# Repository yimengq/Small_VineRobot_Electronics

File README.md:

# Board Design for Vine Robot:

## Overview:
### Gen 1 Board:
- Initially split into 4 total boards, 2 on outside for Sensing board + Power Module, and 2 on inside for POE communication board
- The external tip sensing board is designed based on ESP32 XIAO

### Gen 2 Board:

### Instructions  
To view video stream from ESP32-S3. 
- Follow instructions in ```Software/SoftwareSetup.txt``` to set up the ESP32-S3 and ESP32-EVB as a Wifi access point (Eth2Ap). 
- Upload ```Software/Arduino/CameraWebServer/CameraWebServer.ino``` onto ESP32-S3. 
- Run ```Software/videostream.py``` to view live video. 

### To Do (in progress)
- Achieve 1080p @ 30fps 
- Telemetry for IMU data 
- Two way http (send commands to ESP32-S3)

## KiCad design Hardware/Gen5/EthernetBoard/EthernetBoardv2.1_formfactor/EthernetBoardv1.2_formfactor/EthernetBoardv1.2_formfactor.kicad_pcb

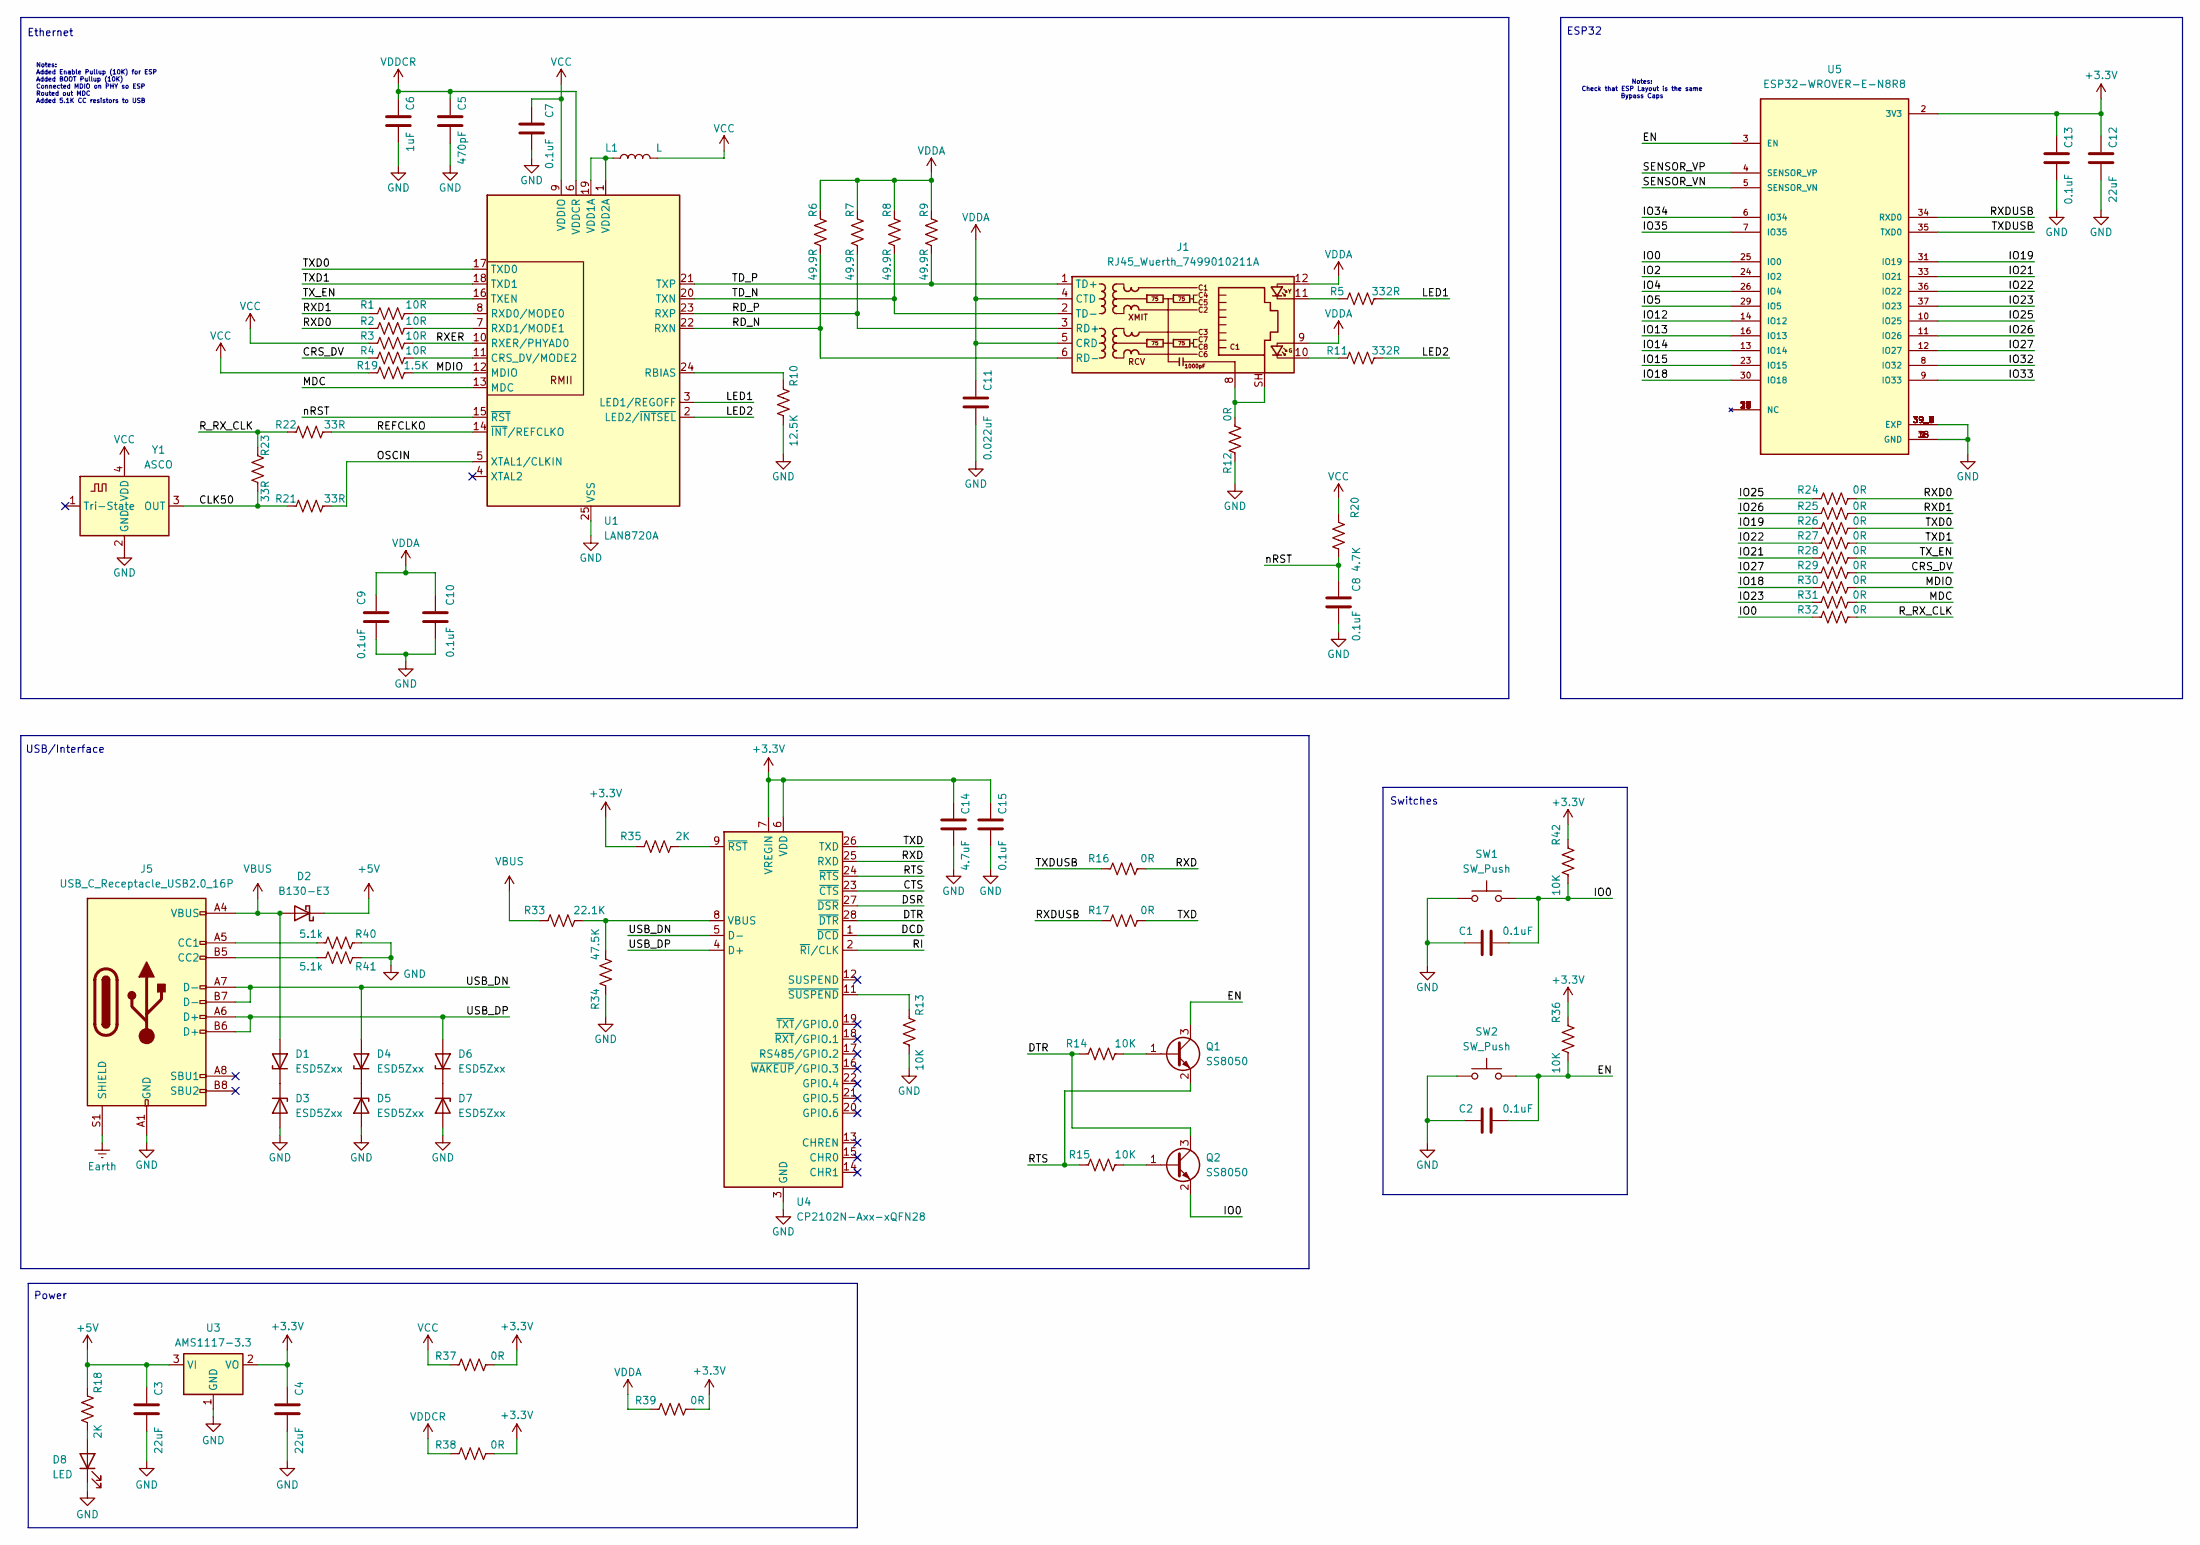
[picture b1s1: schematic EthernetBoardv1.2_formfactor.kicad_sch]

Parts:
C1, C2, C8, C9, C10, C13, C15: 0.1uF; C_0603_1608Metric
C3, C4, C12: 22uF; C_0603_1608Metric
C5: 470pF; C_0603_1608Metric
C6: 1uF; C_0402_1005Metric
C7: 0.1uF; C_0402_1005Metric
C11: 0.022uF; C_0805_2012Metric
C14: 4.7uF; R_0201_0603Metric
D1, D3, D4, D5, D6, D7: ESD5Zxx; D_SOD-523
D2: B130-E3; D_SMA
D8: LED; LED_0603_1608Metric
J1: RJ45_Wuerth_7499010211A; RJ45_Wuerth_7499010211A_Horizontal
J5: USB_C_Receptacle_USB2.0_16P; USB_C_Receptacle_GCT_USB4085
L1: L; L_0603_1608Metric
Q1, Q2: SS8050; SOT-23
R1, R2, R3, R4: 10R; R_0603_1608Metric
R5, R11: 332R; R_0603_1608Metric
R6, R7, R8, R9: 49.9R; R_0402_1005Metric
R10: 12.5K; R_0402_1005Metric
R12, R16, R17, R24, R25, R26, R27, R28, R29, R30, R31, R32, R37, R38, R39: 0R; R_0201_0603Metric
R13, R14, R15: 10K; R_0603_1608Metric
R18: 2K; R_0402_1005Metric
R19: 1.5K; R_0402_1005Metric
R20: 4.7K; R_0402_1005Metric
R21, R22, R23: 33R; R_0402_1005Metric
R33: 22.1K; R_0805_2012Metric
R34: 47.5K; R_0603_1608Metric
R35: 2K; R_0805_2012Metric
R36, R42: 10K; R_0402_1005Metric
R40, R41: 5.1k; R_0603_1608Metric
SW1, SW2: SW_Push; SW_SPST_PTS810
U1: LAN8720A; VQFN-24-1EP_4x4mm_P0.5mm_EP2.5x2.5mm_ThermalVias
U3: AMS1117-3.3; SOT-223-3_TabPin2
U4: CP2102N-Axx-xQFN28; QFN-28-1EP_5x5mm_P0.5mm_EP3.35x3.35mm
U5: ESP32-WROVER-E-N8R8; XCVR_ESP32-WROVER-E-N8R8; PARTREV 1.6
Y1: ASCO; Oscillator_SMD_Abracon_ASCO-4Pin_1.6x1.2mm

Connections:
+3.3V: C4.1, C12.1, C13.1, C14.1, C15.1, R35.1, R36.2, R37.2, R38.2, R39.2, R42.2, U3.2 (VO), U4.6 (VDD), U4.7 (VREGIN), U5.2 (3V3)
+5V: C3.1, D2.1 (K), R18.1, U3.3 (VI)
/CLK50: R21.2, R23.1, Y1.3 (OUT)
/CRS_DV: R4.2, R29.2
/CTS: U4.23 (~CTS)
/DCD: U4.1 (~DCD)
/DSR: U4.27 (~DSR)
/DTR: Q2.3 (C), R14.1, U4.28 (~DTR)
/EN: C2.2, Q1.3 (C), R36.1, SW2.2, U5.3 (EN)
/IO0: C1.2, Q2.2 (E), R32.1, R42.1, SW1.2, U5.25 (IO0)
/IO2: U5.24 (IO2)
/IO4: U5.26 (IO4)
/IO5: U5.29 (IO5)
/IO12: U5.14 (IO12)
/IO13: U5.16 (IO13)
/IO14: U5.13 (IO14)
/IO15: U5.23 (IO15)
/IO18: R30.1, U5.30 (IO18)
/IO19: R26.1, U5.31 (IO19)
/IO21: R28.1, U5.33 (IO21)
/IO22: R27.1, U5.36 (IO22)
/IO23: R31.1, U5.37 (IO23)
/IO25: R24.1, U5.10 (IO25)
/IO26: R25.1, U5.11 (IO26)
/IO27: R29.1, U5.12 (IO27)
/IO32: U5.8 (IO32)
/IO33: U5.9 (IO33)
/IO34: U5.6 (IO34)
/IO35: U5.7 (IO35)
/LED1: R5.1, U1.3 (LED1/REGOFF)
/LED2: R11.1, U1.2 (LED2/~INTSEL)
/MDC: R31.2, U1.13 (MDC)
/MDIO: R19.1, R30.2, U1.12 (MDIO)
/OSCIN: R21.1, U1.5 (XTAL1/CLKIN)
/RD_N: J1.6 (RD-), R6.2, U1.22 (RXN)
/RD_P: J1.3 (RD+), R7.2, U1.23 (RXP)
/REFCLKO: R22.1, U1.14 (~INT/REFCLKO)
/RI: U4.2 (~RI/CLK)
/RTS: Q1.2 (E), R15.1, U4.24 (~RTS)
/RXD: R16.2, U4.25 (RXD)
/RXD0: R2.2, R24.2
/RXD1: R1.1, R25.2
/RXDUSB: R17.1, U5.34 (RXD0)
/RXER: R3.1, U1.10 (RXER/PHYAD0)
/R_RX_CLK: R22.2, R23.2, R32.2
/SENSOR_VN: U5.5 (SENSOR_VN)
/SENSOR_VP: U5.4 (SENSOR_VP)
/TD_N: J1.2 (TD-), R8.2, U1.20 (TXN)
/TD_P: J1.1 (TD+), R9.2, U1.21 (TXP)
/TXD: R17.2, U4.26 (TXD)
/TXD0: R26.2, U1.17 (TXD0)
/TXD1: R27.2, U1.18 (TXD1)
/TXDUSB: R16.1, U5.35 (TXD0)
/TX_EN: R28.2, U1.16 (TXEN)
/USB_DN: D4.2 (A), J5.A7 (D-), J5.B7 (D-), U4.5 (D-)
/USB_DP: D6.2 (A), J5.A6 (D+), J5.B6 (D+), U4.4 (D+)
/nRST: C8.1, R20.1, U1.15 (~RST)
Earth: J5.S1 (SHIELD)
GND: C1.1, C2.1, C3.2, C4.2, C5.2, C6.2, C7.2, C8.2, C9.2, C10.2, C11.2, C12.2, C13.2, C14.2, C15.2, D3.2 (A), D5.2 (A), D7.2 (A), D8.1 (K), J5.A1 (GND), J5.A12 (GND), J5.B1 (GND), J5.B12 (GND), R10.2, R12.2, R13.2, R34.1, R40.1, R41.1, SW1.1, SW2.1, U1.25 (VSS), U3.1 (GND), U4.3 (GND), U4.29 (GND), U5.1 (GND), U5.15 (GND), U5.38 (GND), U5.39_1 (EXP), U5.39_2 (EXP), U5.39_3 (EXP), U5.39_4 (EXP), U5.39_5 (EXP), U5.39_6 (EXP), U5.39_7 (EXP), U5.39_8 (EXP), U5.39_9 (EXP), Y1.2 (GND)
unnamed: D1.1 (K), D3.1 (K)
unnamed: D4.1 (K), D5.1 (K)
unnamed: D6.1 (K), D7.1 (K)
unnamed: D8.2 (A), R18.2
unnamed: J1.8, J1.SH, R12.1
unnamed: J1.10, R11.2
unnamed: J1.11, R5.2
unnamed: J5.A5 (CC1), R40.2
unnamed: J5.B5 (CC2), R41.2
unnamed: Q1.1 (B), R14.2
unnamed: Q2.1 (B), R15.2
unnamed: R4.1, U1.11 (CRS_DV/MODE2)
unnamed: R10.1, U1.24 (RBIAS)
unnamed: R1.2, U1.8 (RXD0/MODE0)
unnamed: R2.1, U1.7 (RXD1/MODE1)
unnamed: L1.1, U1.1 (VDD2A), U1.19 (VDD1A)
unnamed: R33.2, R34.2, U4.8 (VBUS)
unnamed: R35.2, U4.9 (~RST)
unnamed: R13.1, U4.11 (~SUSPEND)
VBUS: D1.2 (A), D2.2 (A), J5.A4 (VBUS), J5.A9 (VBUS), J5.B4 (VBUS), J5.B9 (VBUS), R33.1
VCC: C7.1, L1.2, R3.2, R19.2, R20.2, R37.1, U1.9 (VDDIO), Y1.4 (VDD)
VDDA: C9.1, C10.1, C11.1, J1.4 (CTD), J1.5 (CRD), J1.9, J1.12, R6.1, R7.1, R8.1, R9.1, R39.1
VDDCR: C5.1, C6.1, R38.1, U1.6 (VDDCR)

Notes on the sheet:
Notes: Added Enable Pullup (10K) for ESP Added BOOT Pullup (10K) Connected MDIO on PHY so ESP Routed out MDC Added 5.1K CC resistors to USB
ESP32
Ethernet
USB/Interface
Notes: Check that ESP Layout is the same Bypass Caps
Power
Switches

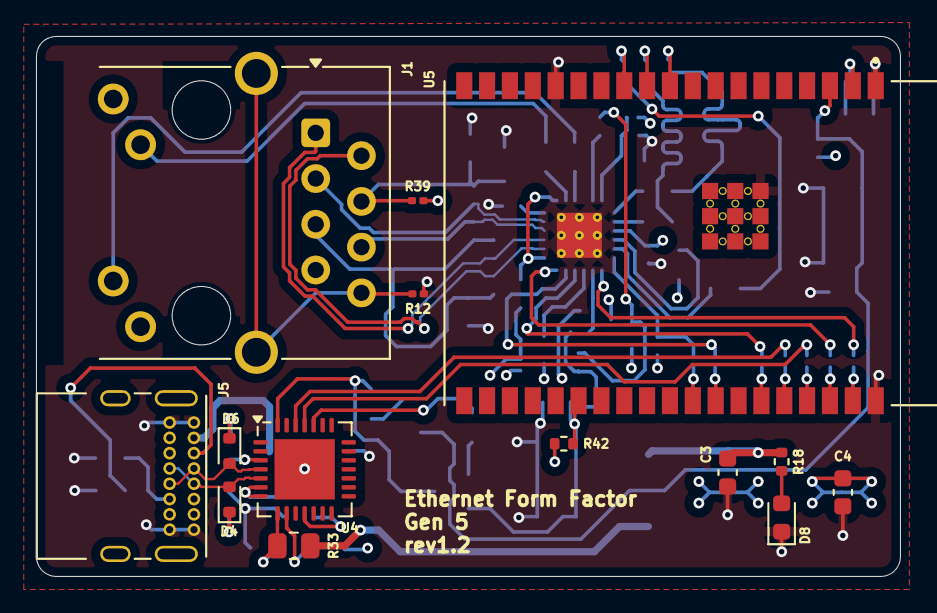
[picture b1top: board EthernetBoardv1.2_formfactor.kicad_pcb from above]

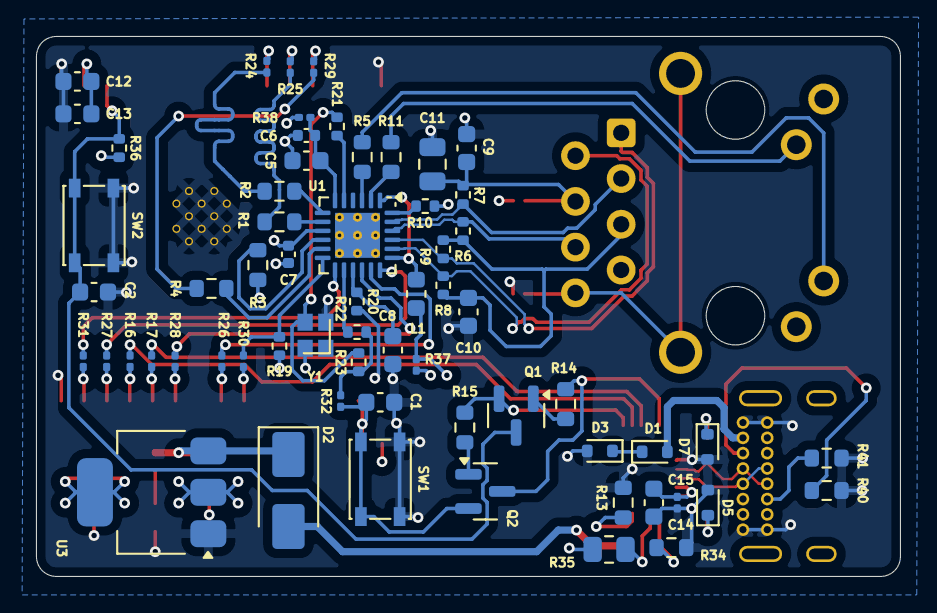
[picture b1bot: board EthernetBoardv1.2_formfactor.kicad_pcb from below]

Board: 4 copper layers, 48.0 x 30.0 mm, 77 parts (63 on the bottom side), 64 nets.

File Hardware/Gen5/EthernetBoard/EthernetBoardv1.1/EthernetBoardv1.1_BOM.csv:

"Id";"Designator";"Footprint";"Quantity";"Designation";"Supplier and ref";
1;"J1";"RJ45_Wuerth_7499010211A_Horizontal";1;"RJ45_Wuerth_7499010211A";;;
2;"C1,C2,C15,C13,C10,C9,C8,C7";"C_0603_1608Metric";8;"0.1uF";;;
3;"TP2,TP1";"TestPoint_Pad_2.0x2.0mm";2;"TestPoint";;;
4;"J6";"PinHeader_1x02_P2.54mm_Vertical";1;"Conn_01x02_Pin";;;
5;"J4";"PinHeader_2x07_P2.54mm_Vertical";1;"Conn_02x07_Odd_Even";;;
6;"R12,R17,R16,R27,R28,R25,R26,R30,R29,R31,R32,R24";"SolderJumper-2_P1.3mm_Bridged2Bar_RoundedPad1.0x1.5mm";12;"0R";;;
7;"R11,R5";"R_0603_1608Metric";2;"332R";;;
8;"R9,R8,R7,R6";"R_0402_1005Metric";4;"49.9R";;;
9;"C11";"C_0805_2012Metric";1;"0.022uF";;;
10;"R10";"R_0402_1005Metric";1;"12.5K";;;
11;"C5";"C_0603_1608Metric";1;"470pF";;;
12;"R20";"R_0402_1005Metric";1;"4.7K";;;
13;"R19";"R_0402_1005Metric";1;"1.5K";;;
14;"R23,R22,R21";"R_0402_1005Metric";3;"33R";;;
15;"SW2,SW1";"SW_SPST_PTS810";2;"SW_Push";;;
16;"J3,J2";"PinHeader_1x19_P2.54mm_Vertical";2;"Conn_01x19_Pin";;;
17;"R18";"R_0402_1005Metric";1;"2K";;;
18;"D8";"LED_0603_1608Metric";1;"LED";;;
19;"C12,C4,C3";"C_0603_1608Metric";3;"22uF";;;
20;"R13,R15,R14";"R_0603_1608Metric";3;"10K";;;
21;"C14";"R_0201_0603Metric";1;"4.7uF";;;
22;"R35";"R_0805_2012Metric";1;"2K";;;
23;"R34";"R_0603_1608Metric";1;"47.5K";;;
24;"R33";"R_0805_2012Metric";1;"22.1K";;;
25;"R4,R3,R2,R1";"R_0603_1608Metric";4;"10R";;;
26;"C6";"C_0402_1005Metric";1;"1uF";;;
27;"J5";"USB_C_Receptacle_GCT_USB4085";1;"USB_C_Receptacle_USB2.0_16P";;;
28;"D6,D3,D4,D1,D7,D5";"D_SOD-523";6;"ESD5Zxx";;;
29;"U5";"XCVR_ESP32-WROVER-E-N8R8";1;"ESP32-WROVER-E-N8R8";;;
30;"U3";"SOT-223-3_TabPin2";1;"AMS1117-3.3";;;
31;"D2";"D_SMA";1;"B130-E3";;;
32;"Q1,Q2";"SOT-23";2;"SS8050";;;
33;"U1";"VQFN-24-1EP_4x4mm_P0.5mm_EP2.5x2.5mm_ThermalVias";1;"LAN8720A";;;
34;"Y1";"Oscillator_SMD_Abracon_ASCO-4Pin_1.6x1.2mm";1;"ASCO";;;
35;"U4";"QFN-28-1EP_5x5mm_P0.5mm_EP3.35x3.35mm";1;"CP2102N-Axx-xQFN28";;;

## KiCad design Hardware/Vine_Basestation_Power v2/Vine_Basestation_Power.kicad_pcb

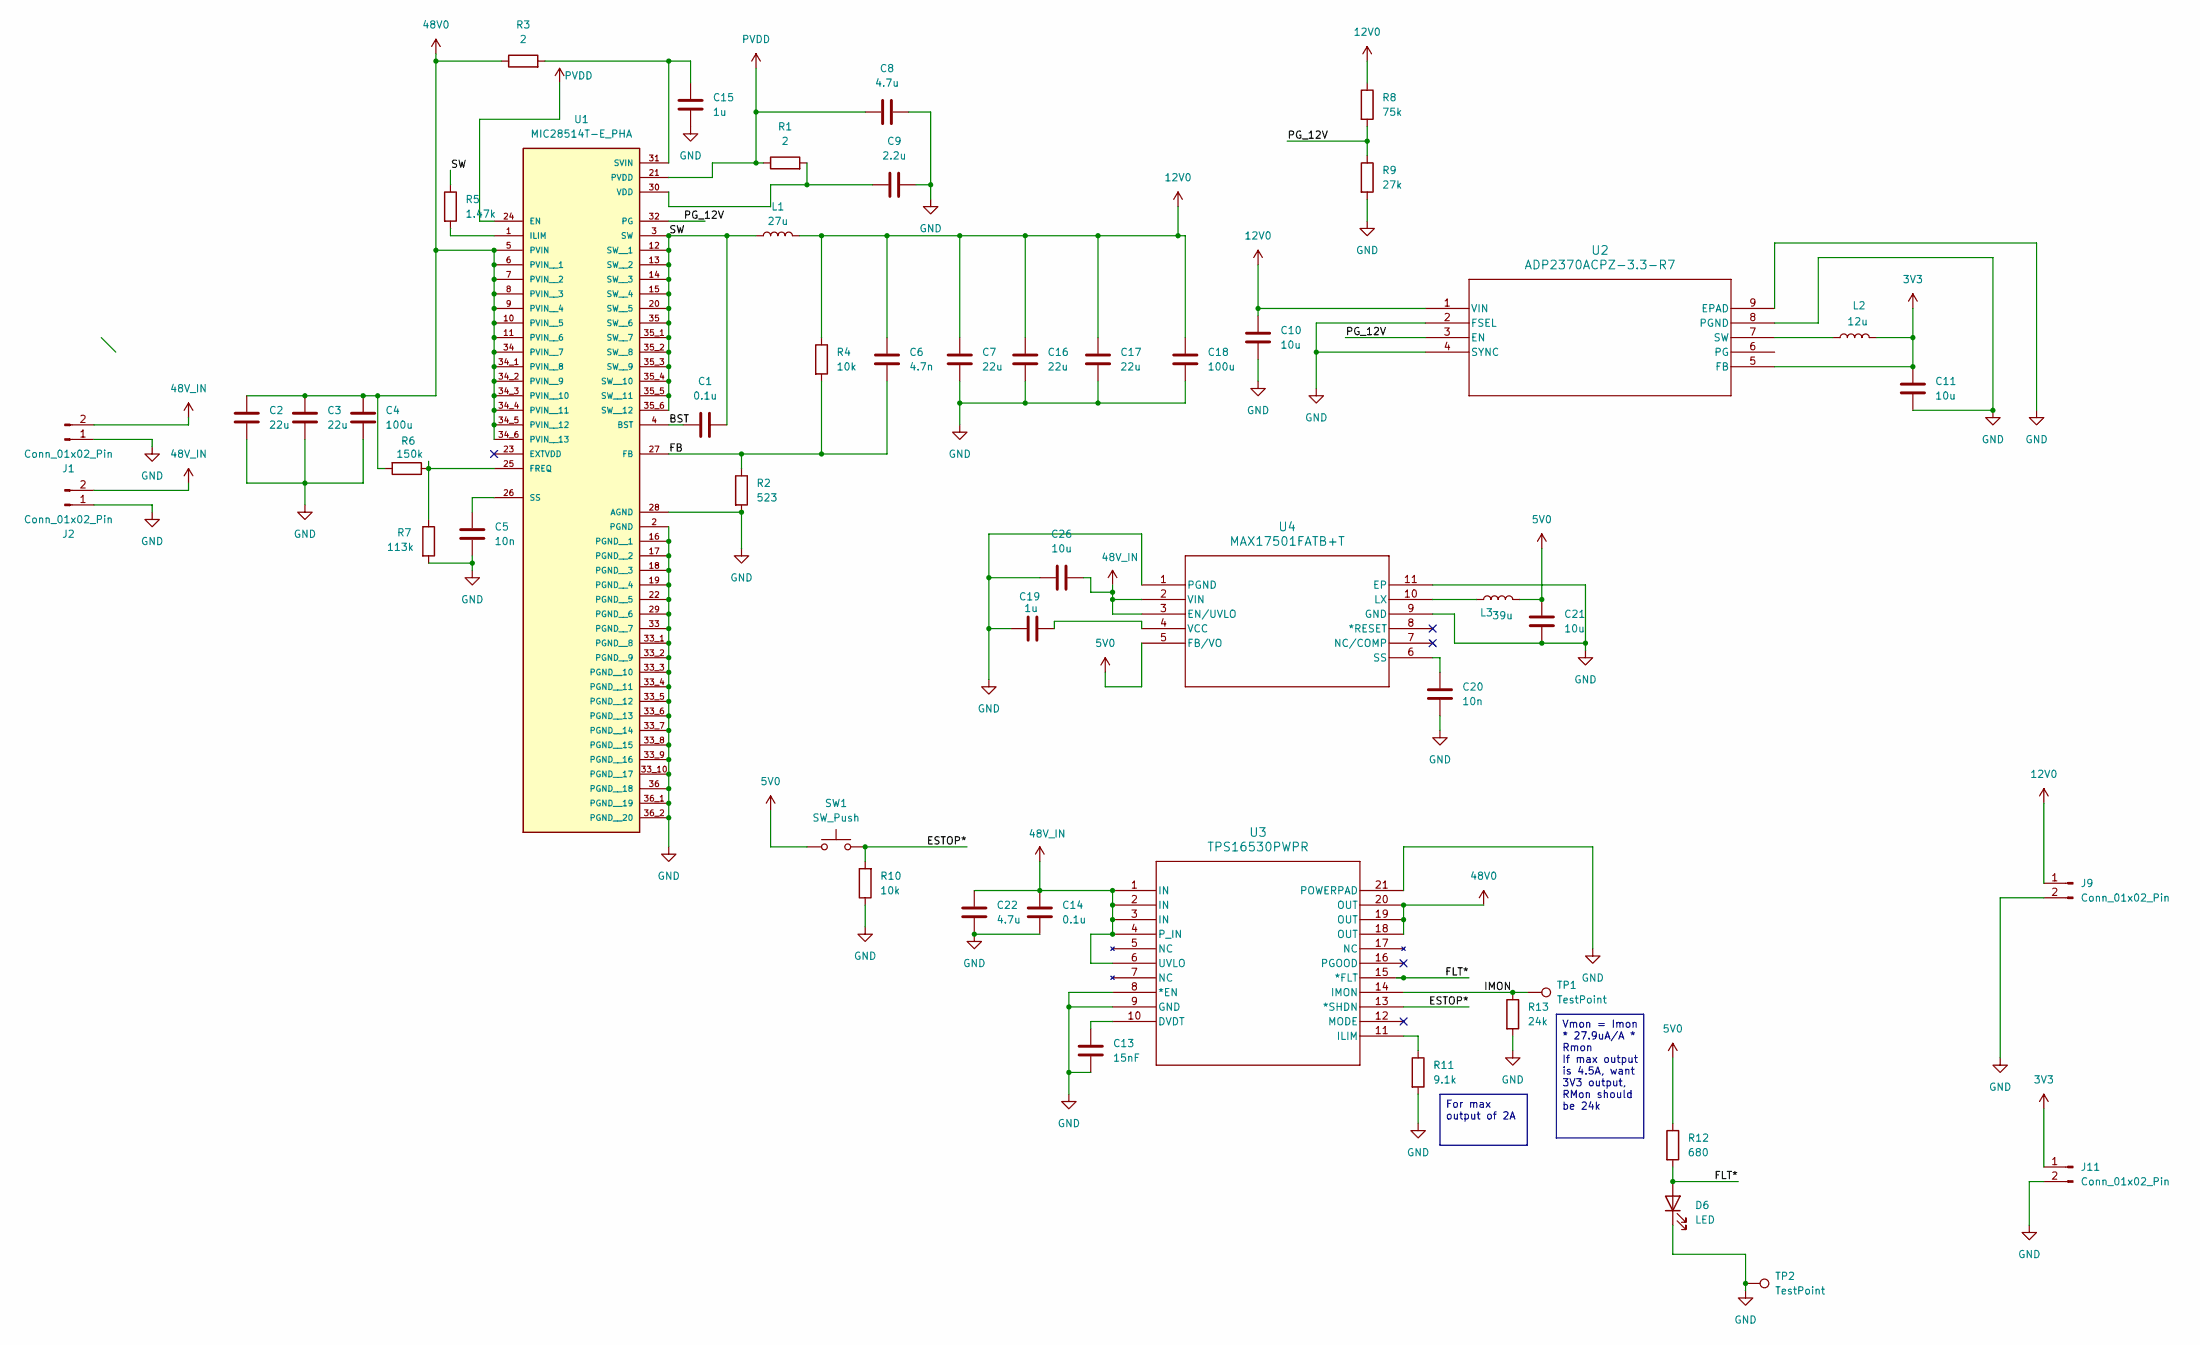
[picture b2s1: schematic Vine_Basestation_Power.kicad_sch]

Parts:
C1, C14: 0.1u; C_0402_1005Metric
C2, C3: 22u; CAP_EEETG2A220UP
C4: 100u; CAP_EEEFK1J101P
C5, C20: 10n; C_0402_1005Metric
C6: 4.7n; C_0402_1005Metric
C7, C16, C17: 22u; C_0805_2012Metric
C8: 4.7u; C_0402_1005Metric
C9: 2.2u; C_0402_1005Metric
C10, C11, C21, C26: 10u; C_0402_1005Metric
C13: 15nF; C_0402_1005Metric
C15, C19: 1u; C_0402_1005Metric
C18: 100u; CP_Radial_D5.0mm_P2.00mm
C22: 4.7u; C_0805_2012Metric
D6: LED; LED_0805_2012Metric
J1, J2: Conn_01x02_Pin; AMASS_XT30U-M_1x02_P5.0mm_Vertical
J9, J11: Conn_01x02_Pin; JST_PH_B2B-PH-SM4-TB_1x02-1MP_P2.00mm_Vertical
L1: 27u; INDM134126X600N
L2: 12u; IND_BOURNS_CC453232
L3: 39u; L_0805_2012Metric
R1, R3: 2; R_0402_1005Metric
R2: 523; R_0402_1005Metric
R4, R10: 10k; R_0402_1005Metric
R5: 1.47k; R_0402_1005Metric
R6: 150k; R_0402_1005Metric
R7: 113k; R_0402_1005Metric
R8: 75k; R_0402_1005Metric
R9: 27k; R_0402_1005Metric
R11: 9.1k; R_0402_1005Metric
R12: 680; R_0402_1005Metric
R13: 24k; R_0402_1005Metric
SW1: SW_Push; JST_PH_B2B-PH-SM4-TB_1x02-1MP_P2.00mm_Vertical
TP1, TP2: TestPoint; TestPoint_Loop_D1.80mm_Drill1.0mm_Beaded
U1: MIC28514T-E_PHA; CONV_MIC28514T-E_PHA; PARTREV E
U2: ADP2370ACPZ-3.3-R7; CP_8_5_ADI
U3: TPS16530PWPR; PWP0020T_TEX
U4: MAX17501FATB+T; 21-0429_T1032N&plus_1_MXM

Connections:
3V3: C11.1, J11.1, L2.2, U2.5 (FB)
5V0: C21.1, L3.2, R12.1, SW1.1, U4.5 (FB/VO)
12V0: C6.1, C7.1, C10.1, C16.1, C17.1, C18.1, J9.1, L1.2, R4.1, R8.1, U2.1 (VIN)
48V0: C2.1, C3.1, C4.1, R3.1, R6.2, U1.5 (PVIN), U1.6 (PVIN__1), U1.7 (PVIN__2), U1.8 (PVIN__3), U1.9 (PVIN__4), U1.10 (PVIN__5), U1.11 (PVIN__6), U1.34 (PVIN__7), U1.34_1 (PVIN__8), U1.34_2 (PVIN__9), U1.34_3 (PVIN__10), U1.34_4 (PVIN__11), U1.34_5 (PVIN__12), U1.34_6 (PVIN__13), U3.18 (OUT), U3.19 (OUT), U3.20 (OUT)
48V_IN: C14.1, C22.1, C26.1, J1.2, J2.2, U3.1 (IN), U3.2 (IN), U3.3 (IN), U3.4 (P_IN), U3.6 (UVLO), U4.2 (VIN), U4.3 (EN/UVLO)
/BST: C1.1, U1.4 (BST)
/ESTOP*: R10.2, SW1.2, U3.13 (*SHDN)
/FB: C6.2, R2.1, R4.2, U1.27 (FB)
/FLT*: D6.2 (A), R12.2, U3.15 (*FLT)
/IMON: R13.1, TP1.1, U3.14 (IMON)
/PG_12V: R8.2, R9.1, U1.32 (PG), U2.3 (EN)
/SW: C1.2, L1.1, R5.1, U1.3 (SW), U1.12 (SW__1), U1.13 (SW__2), U1.14 (SW__3), U1.15 (SW__4), U1.20 (SW__5), U1.35 (SW__6), U1.35_1 (SW__7), U1.35_2 (SW__8), U1.35_3 (SW__9), U1.35_4 (SW__10), U1.35_5 (SW__11), U1.35_6 (SW__12)
GND: C2.2, C3.2, C4.2, C5.2, C7.2, C8.2, C9.2, C10.2, C11.2, C13.2, C14.2, C15.2, C16.2, C17.2, C18.2, C19.1, C20.2, C21.2, C22.2, C26.2, D6.1 (K), J1.1, J2.1, J9.2, J11.2, R2.2, R7.2, R9.2, R10.1, R11.2, R13.2, TP2.1, U1.2 (PGND), U1.16 (PGND__1), U1.17 (PGND__2), U1.18 (PGND__3), U1.19 (PGND__4), U1.22 (PGND__5), U1.28 (AGND), U1.29 (PGND__6), U1.33 (PGND__7), U1.33_1 (PGND__8), U1.33_2 (PGND__9), U1.33_3 (PGND__10), U1.33_4 (PGND__11), U1.33_5 (PGND__12), U1.33_6 (PGND__13), U1.33_7 (PGND__14), U1.33_8 (PGND__15), U1.33_9 (PGND__16), U1.33_10 (PGND__17), U1.36 (PGND__18), U1.36_1 (PGND__19), U1.36_2 (PGND__20), U2.2 (FSEL), U2.4 (SYNC), U2.8 (PGND), U2.9 (EPAD), U3.8 (*EN), U3.9 (GND), U3.21 (POWERPAD), U4.1 (PGND), U4.9 (GND), U4.11 (EP)
unnamed: R6.1, R7.1, U1.25 (FREQ)
unnamed: R5.2, U1.1 (ILIM)
unnamed: C5.1, U1.26 (SS)
unnamed: C15.1, R3.2, U1.31 (SVIN)
unnamed: C9.1, R1.2, U1.30 (VDD)
unnamed: L2.1, U2.7 (SW)
unnamed: C13.1, U3.10 (DVDT)
unnamed: R11.1, U3.11 (ILIM)
unnamed: L3.1, U4.10 (LX)
unnamed: C20.1, U4.6 (SS)
unnamed: C19.2, U4.4 (VCC)
PVDD: C8.1, R1.1, U1.21 (PVDD), U1.24 (EN)

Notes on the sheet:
Vmon = Imon * 27.9uA/A * Rmon If max output is 4.5A, want 3V3 output, RMon should be 24k
For max output of 2A

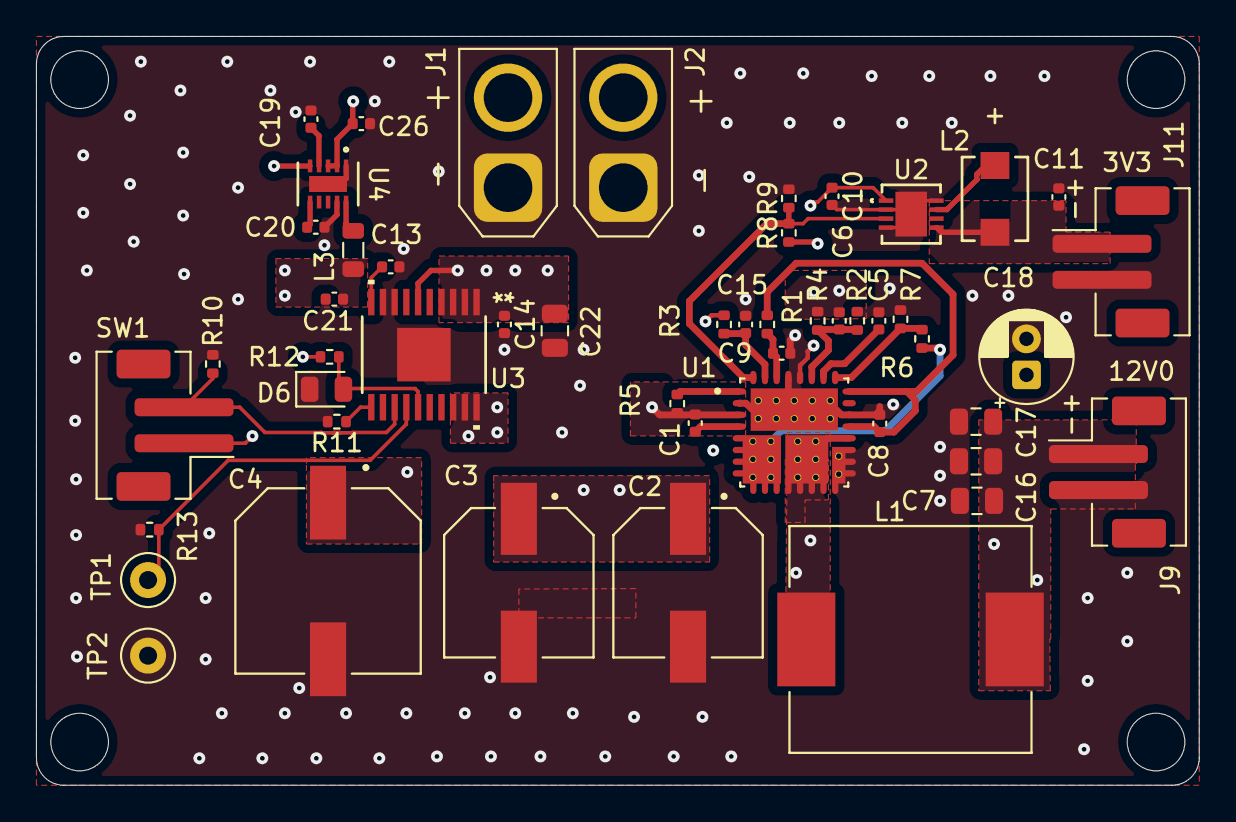
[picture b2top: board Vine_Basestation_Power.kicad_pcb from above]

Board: 4 copper layers, 64.6 x 41.6 mm, 50 parts (0 on the bottom side), 25 nets.

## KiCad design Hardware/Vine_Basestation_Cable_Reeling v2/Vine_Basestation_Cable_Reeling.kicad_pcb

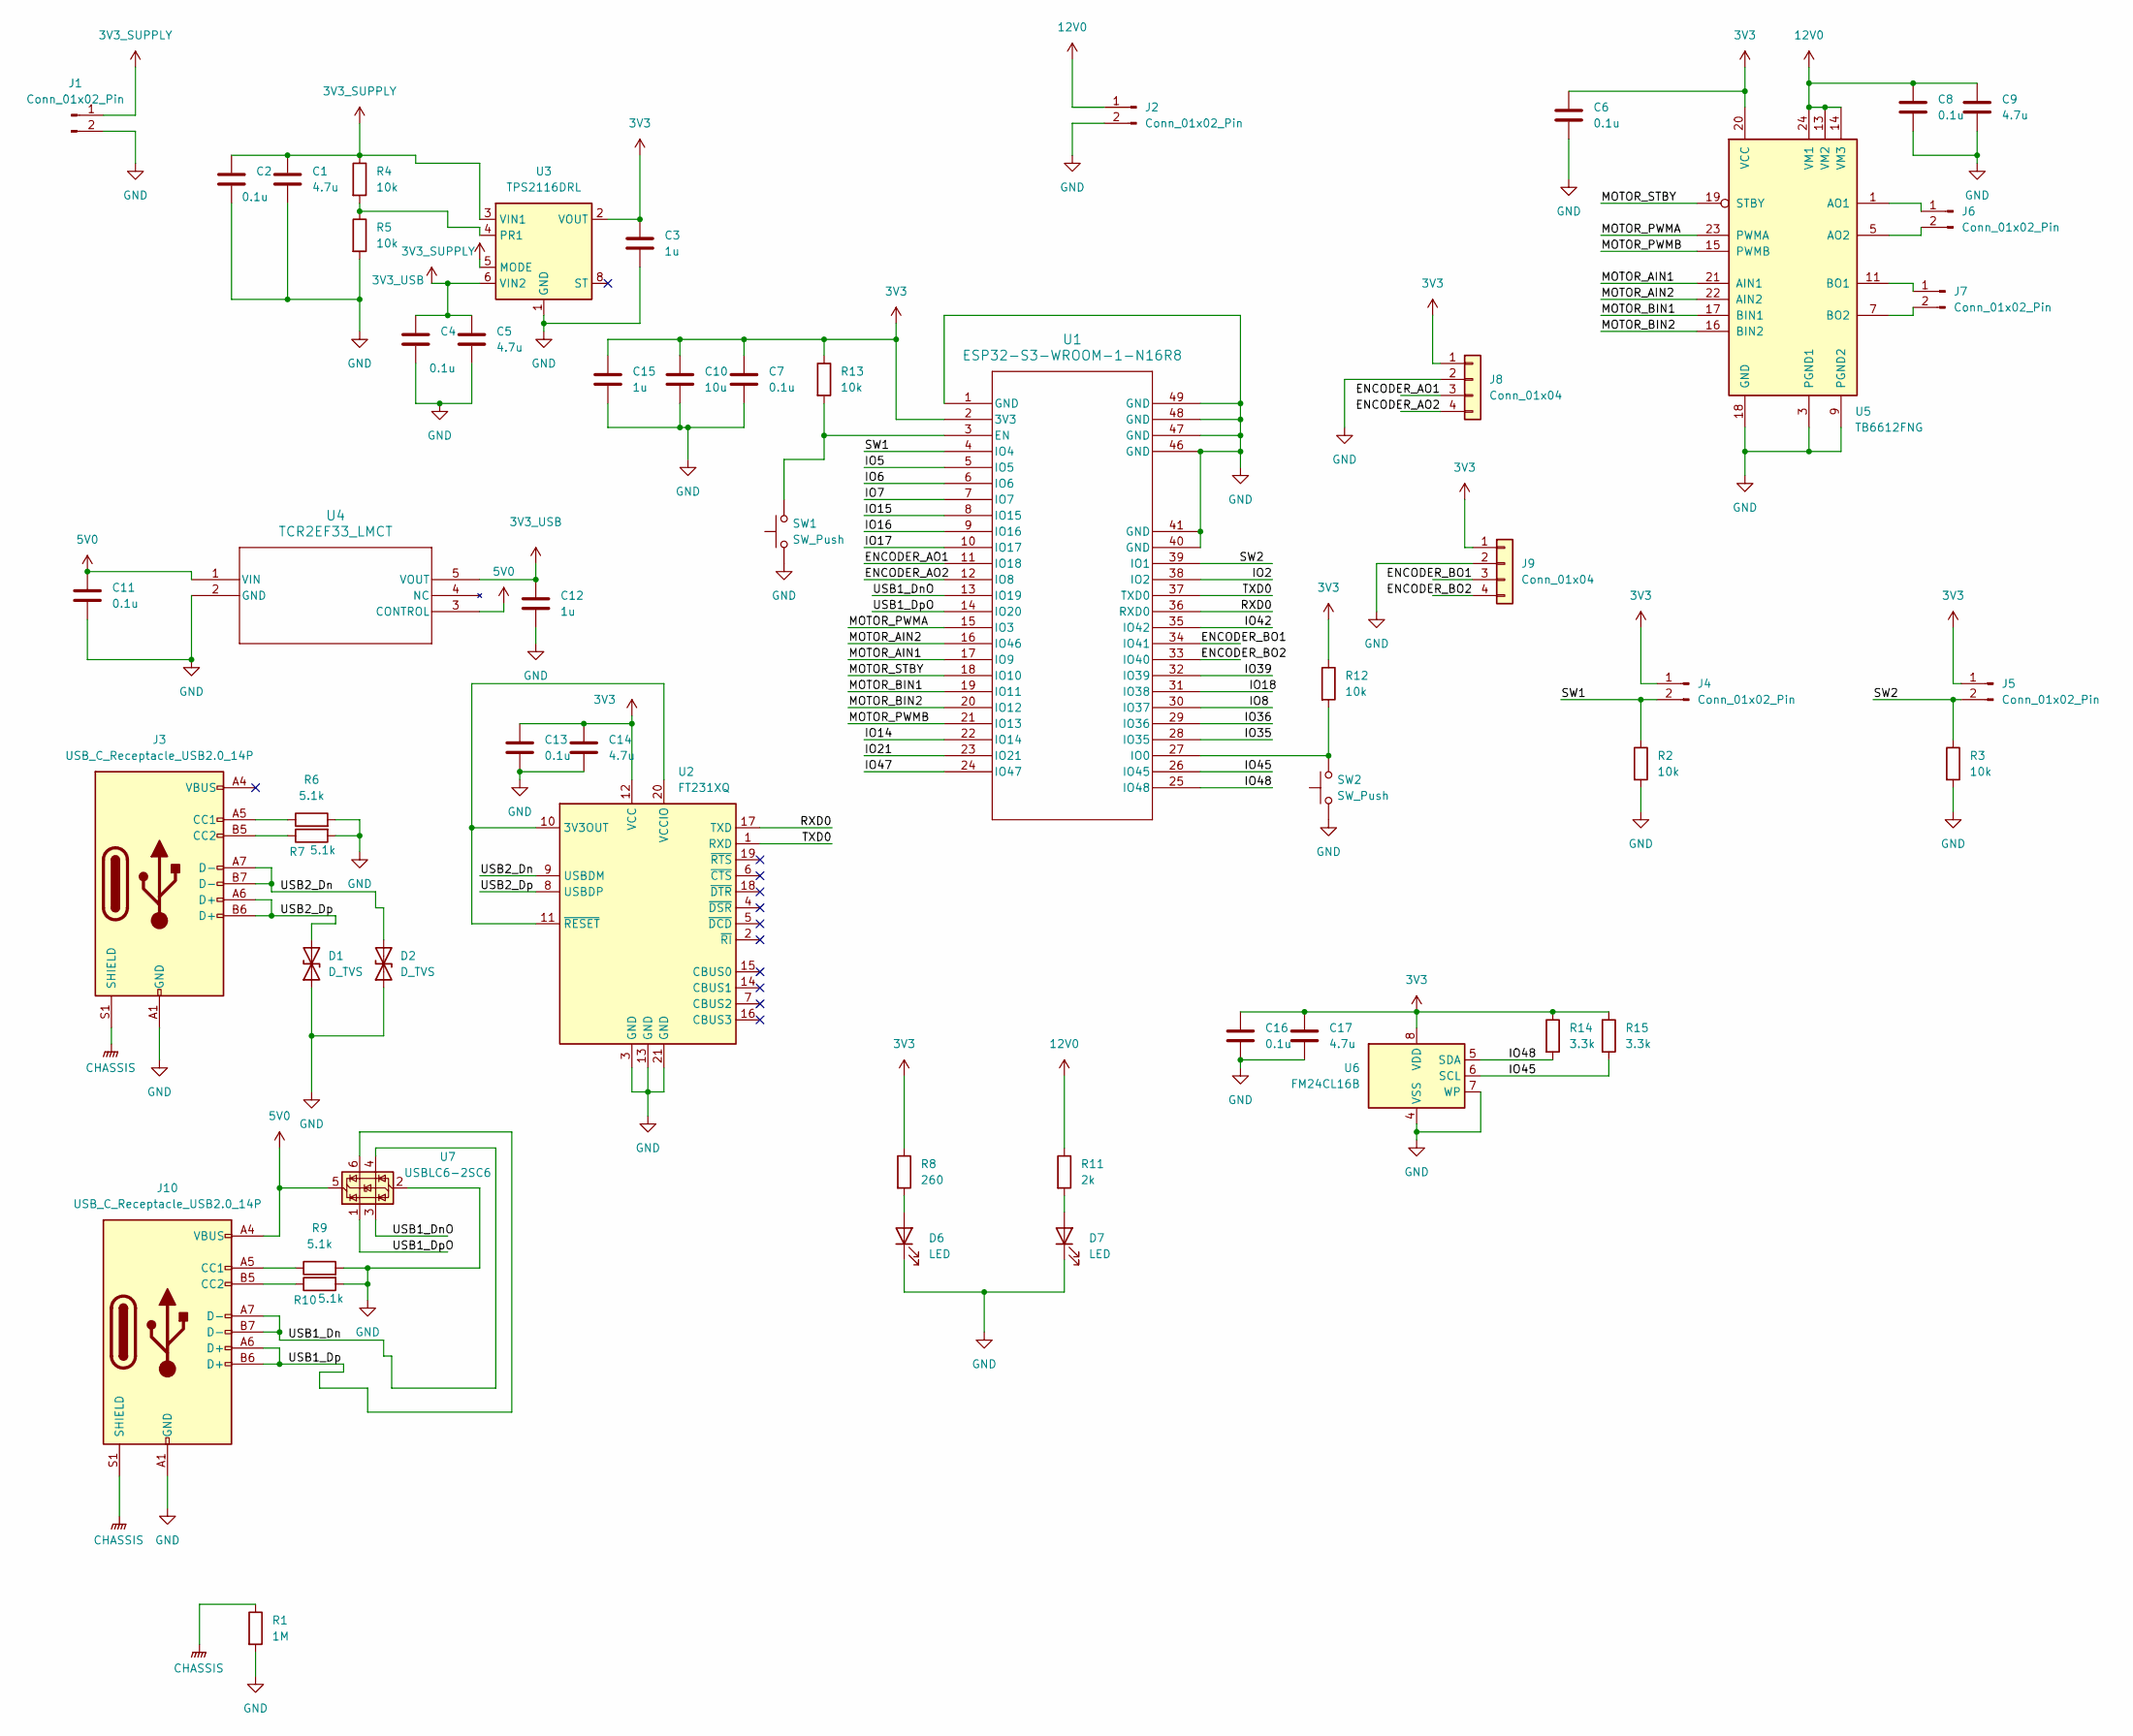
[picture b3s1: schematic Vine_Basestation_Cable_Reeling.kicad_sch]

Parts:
C1, C5, C9, C14, C17: 4.7u; C_0402_1005Metric
C2, C4, C6, C7, C8, C11, C13, C16: 0.1u; C_0402_1005Metric
C3, C12, C15: 1u; C_0402_1005Metric
C10: 10u; C_0402_1005Metric
D1, D2: D_TVS; D_SOD-523
D6, D7: LED; LED_0805_2012Metric
J1, J2, J4, J5, J6, J7: Conn_01x02_Pin; JST_PH_B2B-PH-SM4-TB_1x02-1MP_P2.00mm_Vertical
J3, J10: USB_C_Receptacle_USB2.0_14P; USB_C_Receptacle_GCT_USB4110
J8, J9: Conn_01x04; JST_PH_B4B-PH-SM4-TB_1x04-1MP_P2.00mm_Vertical
R1: 1M; R_0402_1005Metric
R2, R3, R4, R5, R12, R13: 10k; R_0402_1005Metric
R6, R7, R9, R10: 5.1k; R_0402_1005Metric
R8: 260; R_0402_1005Metric
R11: 2k; R_0402_1005Metric
R14, R15: 3.3k; R_0402_1005Metric
SW1, SW2: SW_Push; SW_SPST_B3U-1000P
U1: ESP32-S3-WROOM-1-N16R8; ESP32-S3-WROOM-1_EXP
U2: FT231XQ; QFN-20-1EP_4x4mm_P0.5mm_EP2.5x2.5mm
U3: TPS2116DRL; SOT-583-8
U4: TCR2EF33_LMCT; SOT-25 SMV_TOS
U5: TB6612FNG; SSOP-24_5.3x8.2mm_P0.65mm
U6: FM24CL16B; SOIC-8_3.9x4.9mm_P1.27mm
U7: USBLC6-2SC6; SOT-23-6

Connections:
3V3: C3.1, C6.1, C7.1, C10.1, C13.1, C14.1, C15.1, C16.1, C17.1, J4.1, J5.1, J8.1, J9.1, R8.1, R12.1, R13.1, R14.1, R15.1, U1.2 (3V3), U2.12 (VCC), U3.2 (VOUT), U3.7 (VOUT), U5.20 (VCC), U6.8 (VDD)
3V3_SUPPLY: C1.1, C2.1, J1.1, R4.1, U3.3 (VIN1), U3.5 (MODE)
3V3_USB: C4.1, C5.1, C12.1, U3.6 (VIN2), U4.5 (VOUT)
5V0: C11.1, J10.A4 (VBUS), J10.A9 (VBUS), J10.B4 (VBUS), J10.B9 (VBUS), U4.1 (VIN), U4.3 (CONTROL), U7.5 (VBUS)
12V0: C8.1, C9.1, J2.1, R11.1, U5.13 (VM2), U5.14 (VM3), U5.24 (VM1)
/ENCODER_AO1: J8.3, U1.11 (IO18)
/ENCODER_AO2: J8.4, U1.12 (IO8)
/ENCODER_BO1: J9.3, U1.34 (IO41)
/ENCODER_BO2: J9.4, U1.33 (IO40)
/IO2: U1.38 (IO2)
/IO5: U1.5 (IO5)
/IO6: U1.6 (IO6)
/IO7: U1.7 (IO7)
/IO8: U1.30 (IO37)
/IO14: U1.22 (IO14)
/IO15: U1.8 (IO15)
/IO16: U1.9 (IO16)
/IO17: U1.10 (IO17)
/IO18: U1.31 (IO38)
/IO21: U1.23 (IO21)
/IO35: U1.28 (IO35)
/IO36: U1.29 (IO36)
/IO39: U1.32 (IO39)
/IO42: U1.35 (IO42)
/IO45: R15.2, U1.26 (IO45), U6.6 (SCL)
/IO47: U1.24 (IO47)
/IO48: R14.2, U1.25 (IO48), U6.5 (SDA)
/MOTOR_AIN1: U1.17 (IO9), U5.21 (AIN1)
/MOTOR_AIN2: U1.16 (IO46), U5.22 (AIN2)
/MOTOR_BIN1: U1.19 (IO11), U5.17 (BIN1)
/MOTOR_BIN2: U1.20 (IO12), U5.16 (BIN2)
/MOTOR_PWMA: U1.15 (IO3), U5.23 (PWMA)
/MOTOR_PWMB: U1.21 (IO13), U5.15 (PWMB)
/MOTOR_STBY: U1.18 (IO10), U5.19 (STBY)
/RXD0: U1.36 (RXD0), U2.17 (TXD)
/SW1: J4.2, R2.1, U1.4 (IO4)
/SW2: J5.2, R3.1, U1.39 (IO1)
/TXD0: U1.37 (TXD0), U2.1 (RXD)
/USB1_Dn: J10.A7 (D-), J10.B7 (D-), U7.4 (I/O2)
/USB1_DnO: U1.13 (IO19), U7.3 (I/O2)
/USB1_Dp: J10.A6 (D+), J10.B6 (D+), U7.6 (I/O1)
/USB1_DpO: U1.14 (IO20), U7.1 (I/O1)
/USB2_Dn: D2.2 (A2), J3.A7 (D-), J3.B7 (D-), U2.9 (USBDM)
/USB2_Dp: D1.2 (A2), J3.A6 (D+), J3.B6 (D+), U2.8 (USBDP)
CHASSIS: J3.S1 (SHIELD), J10.S1 (SHIELD), R1.1
GND: C1.2, C2.2, C3.2, C4.2, C5.2, C6.2, C7.2, C8.2, C9.2, C10.2, C11.2, C12.2, C13.2, C14.2, C15.2, C16.2, C17.2, D1.1 (A1), D2.1 (A1), D6.1 (K), D7.1 (K), J1.2, J2.2, J3.A1 (GND), J3.A12 (GND), J3.B1 (GND), J3.B12 (GND), J8.2, J9.2, J10.A1 (GND), J10.A12 (GND), J10.B1 (GND), J10.B12 (GND), R1.2, R2.2, R3.2, R5.2, R6.2, R7.2, R9.2, R10.2, SW1.1, SW2.1, U1.1 (GND), U1.40 (GND), U1.41 (GND), U1.46 (GND), U1.47 (GND), U1.48 (GND), U1.49 (GND), U2.3 (GND), U2.13 (GND), U2.21 (GND), U3.1 (GND), U4.2 (GND), U5.3 (PGND1), U5.4 (PGND1), U5.9 (PGND2), U5.10 (PGND2), U5.18 (GND), U6.4 (VSS), U6.7 (WP), U7.2 (GND)
unnamed: D6.2 (A), R8.2
unnamed: D7.2 (A), R11.2
unnamed: J3.A5 (CC1), R6.1
unnamed: J3.B5 (CC2), R7.1
unnamed: J6.1, U5.1 (AO1), U5.2 (AO1)
unnamed: J6.2, U5.5 (AO2), U5.6 (AO2)
unnamed: J7.1, U5.11 (BO1), U5.12 (BO1)
unnamed: J7.2, U5.7 (BO2), U5.8 (BO2)
unnamed: J10.A5 (CC1), R9.1
unnamed: J10.B5 (CC2), R10.1
unnamed: R13.2, SW1.2, U1.3 (EN)
unnamed: R12.2, SW2.2, U1.27 (IO0)
unnamed: U2.10 (3V3OUT), U2.11 (~RESET), U2.20 (VCCIO)
unnamed: R4.2, R5.1, U3.4 (PR1)
